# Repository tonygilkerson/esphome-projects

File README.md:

# esphome-projects

My ESPHome Projects

## Next

Plan: Send typed text from HA to ESPHome
TL;DR — Preferred approach: use a Home Assistant input_text helper + an ESPHome api action that accepts a string and publishes it to a text_sensor (no extra broker, low latency, secure via api.encryption).

Steps
* Add an api.actions handler, a globals string, and a text_sensor to cover-controller.yaml so the device can receive and store text.
* Create an input_text helper in Home Assistant (input_text.garage_message) for user input.
* Add an HA automation that triggers on input_text.garage_message change and calls the generated esphome.<node>_<action> service to send the text.

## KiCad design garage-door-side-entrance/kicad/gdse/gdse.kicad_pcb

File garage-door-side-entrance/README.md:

# Garage Door Side Entrance

A cover controller for the side garage door.

## Resources

### KiCad

* [KiCad 9.0 - Getting Started Part 1: Intro & Download | DigiKey](https://youtu.be/0WCi1rhueH4?si=1Ts0QHfG8CvHoBf-)
* [Snapeda](https://www.snapeda.com/) - Has footprint files for Adafruit products

### JST

* [Adafruit](https://www.adafruit.com/product/4423) - 2.5mm Pitch Connector Kit - JST XH Compatible - 560 Piece Kit
* [DigiKey B4B-XH-A](https://www.digikey.com/en/products/detail/jst-sales-america-inc/B4B-XH-A/1651047)
* [JST Wire Connectors](https://www.jst-mfg.com/product/index.php?series=683) - Find part number here, use to search on DigiKey

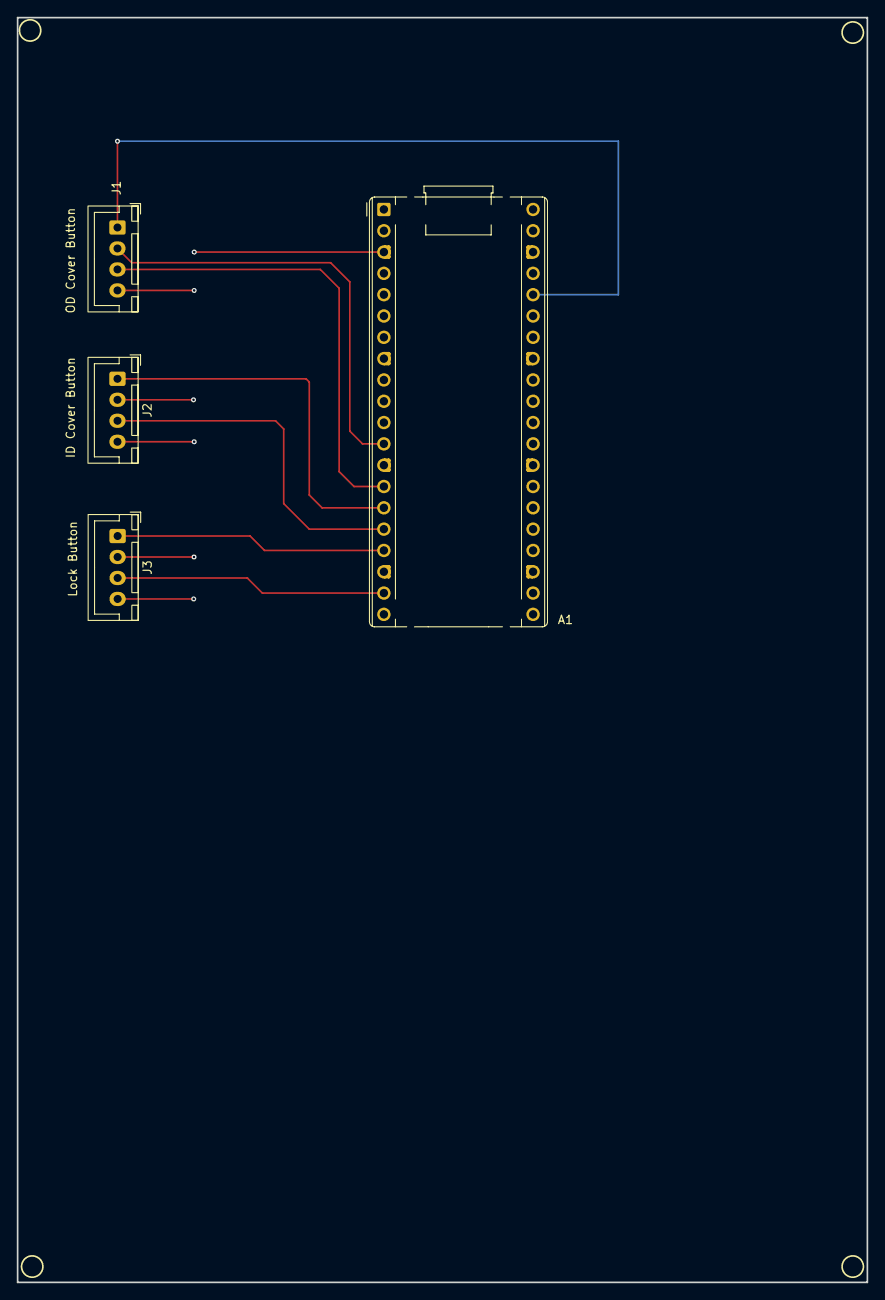
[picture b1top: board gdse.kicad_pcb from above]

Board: 2 copper layers, 101.3 x 150.7 mm, 4 parts (0 on the bottom side), 8 nets.

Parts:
A1: RaspberryPi_Pico_W; RaspberryPi_Pico_Common_THT
J1, J2, J3: Conn_01x04; JST_XH_B4B-XH-A_1x04_P2.50mm_Vertical

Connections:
/3v3: A1.36 (3V3), J1.1
/ID Cover Button | GP12 | 6-16: A1.16 (GPIO12), J2.3
/Is Active LED | GP9 | 3-12: A1.12 (GPIO9), J1.2
/Locked Button | GP14 | 8-19: A1.19 (GPIO14), J3.3
/Locked LED | GP13 | 7-17: A1.17 (GPIO13), J3.1
/OD Cover Button | GP10 |4-14: A1.14 (GPIO10), J1.3
/Run LED | GP11 | 5-15: A1.15 (GPIO11), J2.1
GND: A1.3 (GND), A1.8 (GND), A1.13 (GND), A1.18 (GND), A1.23 (GND), A1.28 (GND), A1.38 (GND), J1.4, J2.2, J2.4, J3.2, J3.4

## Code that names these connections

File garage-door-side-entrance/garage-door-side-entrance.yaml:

esphome:
  name: garage-door-side-entrance
  friendly_name: Garage Door Side Entrance Controller
  on_boot:
    - priority: -100.0 # At this priority, pretty much everything should already be initialized.
      then:
        # DEVTODO turn off (unlocked) for testing
        # - switch.turn_on: lock_switch
        - switch.turn_off: lock_switch
        - output.turn_on: run_led
rp2040:
  board: rpipicow

# DEVTODO - Delete if not used?
# globals:
#   - id: is_cover_locked
#     type: bool
#     restore_value: no
#     initial_value: 'true'

# Enable logging
logger:

# Enable Home Assistant API
api:
  encryption:
    key: !secret api_encryption_key

# Allow Over-The-Air updates  
ota:
  - platform: esphome
    password: !secret ota-password

wifi:
  ssid: !secret wifi_ssid
  password: !secret wifi_password

  # Enable fallback hotspot in case wifi connection fails
  ap:
    ssid: "GDO Fallback Hotspot"
    password: !secret wifi_password

#
# LEDs
#    
output:
  - platform: gpio
    pin: GPIO9
    id: is_active_led
  
  - platform: gpio
    pin: GPIO11
    id: run_led
  
  - platform: gpio
    pin: GPIO13
    id: lock_led

#
# Buttons
#
binary_sensor:
  - platform: gpio
    pin:
      number: GPIO10
      mode: INPUT_PULLUP
      inverted: true
    name: "Outdoor Cover Button"
    id: od_cover_button
    on_press:
      then:
        - logger.log: "👉 BUTTON Press - od_cover_button"
        - if:
            condition:
              switch.is_on: lock_switch
            then:
              - logger.log: "❌ IGNORED Press - cover is locked"
            else:
              - logger.log: "✅ Toggle - toggle the cover"
              - homeassistant.service:
                  service: cover.toggle
                  data:
                    entity_id: cover.garage_door_opener_c0f8d0_side_door_garage_door

  - platform: gpio
    pin:
      number: GPIO12
      mode: INPUT_PULLUP
      inverted: true
    name: "Indoor Cover Button"
    id: id_cover_button
    on_press:
      then:
        - logger.log: "👉 BUTTON Press - id_cover_button"
        - logger.log: "✅ Toggle - toggle the cover"
        - homeassistant.service:
            service: cover.toggle
            data:
              entity_id: cover.garage_door_opener_c0f8d0_side_door_garage_door

  - platform: gpio
    pin:
      number: GPIO14
      mode: INPUT_PULLUP
      inverted: true
    name: "Lock Button"
    id: lock_button
    on_press:
      then:
        - logger.log: "👉 BUTTON Press - lock_button"
        - switch.toggle: lock_switch

#
# Switches
#
switch:
  - platform: output
    name: "Lock Switch"
    output: lock_led
    id: lock_switch
    on_turn_on:
      then:
        - logger.log: "🔒 LOCK - lock_switch turned ON"
        - output.turn_on: lock_led
    on_turn_off:
      then:
        - logger.log: "🔒 UNLOCK - lock_switch turned OFF"
        - output.turn_off: lock_led

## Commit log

2026-01-18 init
2026-01-18 next feat
2026-01-18 wireing
2026-01-26 lora receive works
2026-01-26 ignore .DS_Store
2026-01-31 update drawing
2026-01-31 update png
2026-01-31 lora-hub works
2026-02-02 lora-hub-proto
2026-02-05 GDO side cover
2026-02-07 gdo side entry working
2026-02-08 add kicad
2026-02-08 remove zips
2026-02-08 kicad work
2026-02-09 cleanup
2026-02-10 added buttons to sch
2026-02-10 kcad work
2026-02-11 add jst xh connectors
2026-02-15 start putting it together
2026-02-17 gdo side entrance proto1
